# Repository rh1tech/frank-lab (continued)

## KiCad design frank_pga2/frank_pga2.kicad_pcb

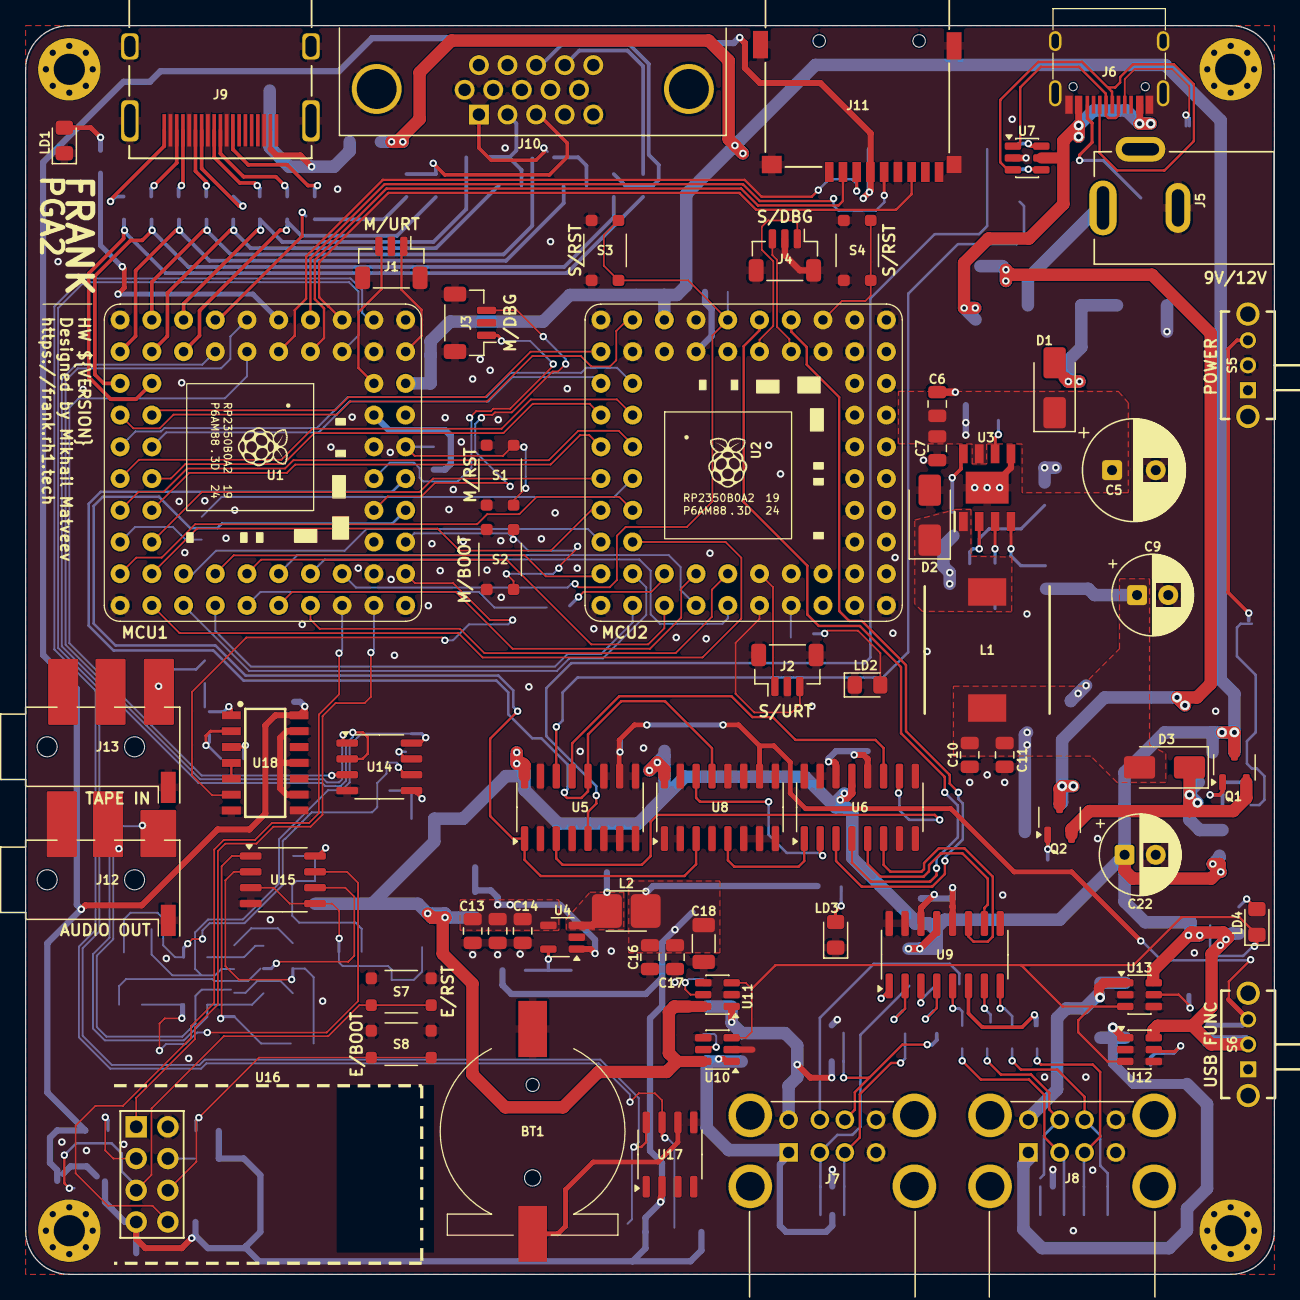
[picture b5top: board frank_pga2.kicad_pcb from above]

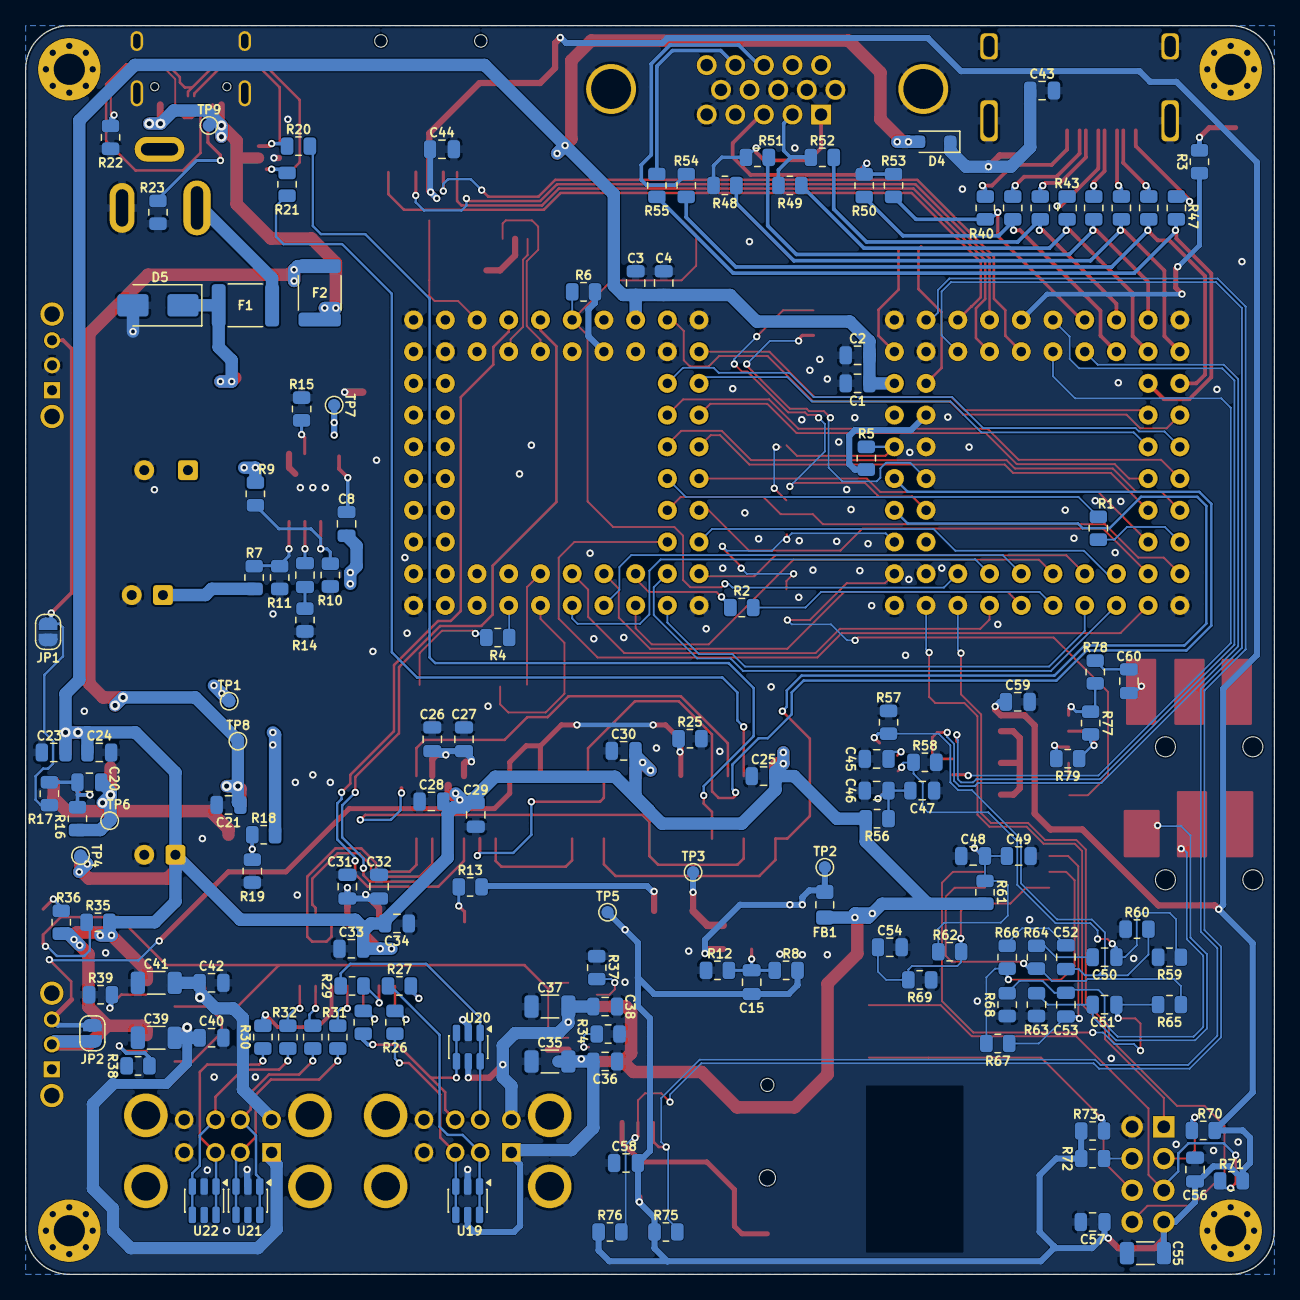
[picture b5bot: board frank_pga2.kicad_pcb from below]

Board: 2 copper layers, 100.0 x 100.0 mm, 212 parts (144 on the bottom side), 173 nets.

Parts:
BT1: Battery_CR1220
C1, C3, C10, C11, C12, C13, C16, C17, C21, C23, C45, C46, C48, C50, C51, C52, C53, C54, C56: 10u 16V; C_0805_2012Metric
C2, C4, C7, C8, C14, C24, C25, C27, C29, C30, C32, C34, C36, C38, C40, C42, C43, C44, C47, C49, C57, C58, C59, C60: 100n 50V; C_0805_2012Metric
C5: 680u 25V; C_Radial_D8.0mm_P3.50mm
C6: 10u 25V; C_0805_2012Metric
C9, C22: 220u 10V; C_Radial_D6.3mm_P2.50mm
C15: 22p 50V; C_0805_2012Metric
C18, C35, C37, C39, C41, C55: 100u 10V; C_1206_3216Metric
C19: 150p 50V; C_0805_2012Metric
C20, C26, C31: 1u 16V; C_0805_2012Metric
C28, C33: 4.7u 16V; C_0805_2012Metric
D1, D2, D3: SS34; D_SMA
D4: 1N5819WS; D_SOD-323
D5: SMAJ15A; D_SMA
F1, F2: 1.5A 24V; Fuse_1812_4532Metric
FB1: 600R@100MHz 2A; L_0805_2012Metric
H1, H2, H3, H4: Hole 2.5mm; MountingHole_2.5mm_Pad_Via
J1: UART M; JST_SH_1x03_P1.00mm_Vertical
J2: UART S; JST_SH_1x03_P1.00mm_Vertical
J3, J4: DEBUG; JST_SH_1x03_P1.00mm_Vertical
J5: DC 9-12V; BarrelJack_DC-005
J6: USB4215-03-A; USB_C_Receptacle
J7, J8: SS-52100-004; USB_A_Stacked
J9: DC3RX19JA2; HDMI_Female
J10: VGA; DSUB-15_Female
J11: 104031-0811; MicroSD_SMD_Long
J12: PJ-320D; AudioJack_3.5mm_PJ320D_AudioOut
J13: PJ-320D; AudioJack_3.5mm_PJ320D_TapeIn
JP1: Force On; SolderJumper-2_P1.3mm_Open_RoundedPad1.0x1.5mm
JP2: USB Debug; SolderJumper-2_P1.3mm_Open_RoundedPad1.0x1.5mm
L1: 22u; Inductor_CDRH104RNP
L2: 2.2u; L_Cenker_CKCS3015_HandSolder
LD1, LD2: Blue; LED_0805
LD3: Green; LED_0805
LD4: Red; LED_0805
Q1, Q2: AO3401A; SOT-23-3L_AOS
R1, R2: 33R; R_0805_2012Metric
R3, R4, R54, R55, R56, R61: 100R; R_0805_2012Metric
R5, R6, R17, R25, R59, R60, R62, R64, R66, R69, R70, R71, R72, R73: 10K; R_0805_2012Metric
R7, R65, R67: 47K; R_0805_2012Metric
R8, R9, R14, R15, R16, R19, R34, R35, R37, R38, R39, R77, R79: 100K; R_0805_2012Metric
R10: 30K; R_0805_2012Metric
R11: 8.2K; R_0805_2012Metric
R12: 22K; R_0805_2012Metric
R13, R18, R36, R51, R52, R53: 1K; R_0805_2012Metric
R20, R21, R26, R27, R28, R29, R30, R31, R32, R33: 22R; R_0805_2012Metric
R22, R23: 5.1K; R_0805_2012Metric
R40, R41, R42, R43, R44, R45, R46, R47: 270R; R_0805_2012Metric
R48, R49, R50: 330R; R_0805_2012Metric
R57, R58: 470R; R_0805_2012Metric
R63, R68: 20K; R_0805_2012Metric
R75, R76, R78: 4.7K; R_0805_2012Metric
S1, S3: RP Reset; Button_SMD_3x4x2mm
S2, S4: RP Boot; Button_SMD_3x4x2mm
S5: POWER; Switch_Slide_SK12D07VG3NS
S6: USB MODE; Switch_Slide_SK12D07VG3NS
S7: ESP Reset; Button_SMD_3x4x2mm
S8: ESP Boot; Button_SMD_3x4x2mm
TP1: +5V_DC; TestPoint_Pad_D1.0mm
TP2: +5V_BUCK; TestPoint_Pad_D1.0mm
TP3: LX; TestPoint_Pad_D1.0mm
TP4: VBUS; TestPoint_Pad_D1.0mm
TP5: +3V3; TestPoint_Pad_D1.0mm
TP6: +5V_SEL; TestPoint_Pad_D1.0mm
TP7: VIN_PROT; TestPoint_Pad_D1.0mm
TP8: VBUS_USB_F; TestPoint_Pad_D1.0mm
TP9: VBUS_USB; TestPoint_Pad_D1.0mm
U1, U2: Pimoroni PGA2350; PGA2350
U3: MP1584EN; SOIC-9_P1.27mm
U4: SY8089AAAC; SOT-23-5
U5, U8: 74HC4052D; SOP-16_P1.27mm
U6, U9: MW7211A; SOP-16_P1.27mm
U7, U19, U20, U21, U22: USBLC6-2SC6; SOT-23-6
U10, U11, U12, U13: CH217K; SOT-23-6
U14: TDA1387T; SO-8
U15: LM358; SO-8
U16: ESP-01 socket; ESP-01S
U17: DS3231MZ; SO-8
U18: CD4069UBM; SOIC-14_P1.27mm

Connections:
+3V3: C15.1, C16.1, C17.1, C18.1, C44.2, C55.1, C56.1, C57.1, C58.1, C59.1, J11.4 (VDD), L2.2, R8.1, R13.1, R70.1, R71.1, R72.1, R73.1, R75.2, R76.2, TP5.1 (1_1), U16.7 (VCC), U17.2 (VCC), U18.14 (VDD)
+5V_DC: C9.1, C10.1, C11.2, D3.2 (A), L1.2, R7.1, R18.1, TP1.1 (1_1)
+5V_SEL: C20.1, D3.1 (K), Q1.2 (S), Q2.2 (S), R16.1, TP6.1 (1_1)
/Audio/AMP_OUTL: C51.2, J12.T, R63.2
/Audio/AMP_OUTR: C53.2, J12.R, R68.2
/Audio/TDA_L: C50.1, R58.2, R59.1, U14.6 (A_LEFT)
/Audio/TDA_R: C52.1, R57.1, R60.1, U14.8 (A_RIGHT)
/ESP-01/ESP_EN: R70.2, U16.3 (CH_PD)
/ESP-01/ESP_GPIO0: R73.2, S8.1, S8.3, U16.6 (GPIO0)
/ESP-01/ESP_GPIO2: R72.2, U16.4 (GPIO2)
/ESP-01/ESP_RST: R71.2, S7.1, S7.3, U16.5 (RST)
/HUB2_UP_DM: U6.5 (DM2), U9.10 (DMU)
/HUB2_UP_DP: U6.6 (DP2), U9.11 (DPU)
/LED_M_A: LD1.2 (A), R3.2
/LED_S_A: LD2.2 (A), R4.2
/M0_UM_TX: J1.1, U1.61 (GP0)
/M1_UM_RX: J1.3, U1.62 (GP1)
/M2_RT_SDA: R76.1, U1.2 (GP2), U17.7 (SDA)
/M3_RT_SCL: R75.1, U1.3 (GP3), U17.8 (SCL)
/M4_SD_DAT0: J11.7 (DAT0), U1.4 (GP4)
/M5_SD_DAT3: J11.2 (DAT3/CD), U1.5 (GP5)
/M6_SD_CLK: J11.5 (CLK), U1.6 (GP6)
/M7_SD_CMD: J11.3 (CMD), U1.7 (GP7)
/M8_LD: R3.1, U1.8 (GP8)
/M9_AU_DATA: U1.9 (GP9), U14.3 (DATA)
/M10_AU_SCLK: U1.10 (GP10), U14.1 (SCLK)
/M11_AU_LRCK: U1.11 (GP11), U14.2 (LRCK)
/M12_HV_CLK-_B0: R40.2, R53.1, U1.12 (GP12)
/M13_HV_CLK+_B1: R41.2, R50.1, U1.13 (GP13)
/M14_HV_D0-_G0: R42.2, R52.1, U1.14 (GP14)
/M15_HV_D0+_G1: R43.2, R49.1, U1.15 (GP15)
/M16_HV_D1-_R0: R44.2, R51.1, U1.16 (GP16)
/M17_HV_D1+_R1: R45.2, R48.1, U1.17 (GP17)
/M18_HV_D2-_HS: R46.2, R54.2, U1.19 (GP18)
/M19_HV_D2+_VS: R47.2, R55.2, U1.20 (GP19)
/M20_S1_LK_A_D0: U1.21 (GP20), U2.62 (GP1)
/M21_S2_LK_A_D1: U1.22 (GP21), U2.2 (GP2)
/M22_S3_LK_A_D2: U1.23 (GP22), U2.3 (GP3)
/M23_S4_LK_A_D3: U1.24 (GP23), U2.4 (GP4)
/M24_S5_LK_A_D4: U1.25 (GP24), U2.5 (GP5)
/M25_S6_LK_A_D5: U1.26 (GP25), U2.6 (GP6)
/M26_S7_LK_A_D6: U1.27 (GP26), U2.7 (GP7)
/M27_S8_LK_A_D7: U1.28 (GP27), U2.8 (GP8)
/M28_LK_A_CLK: R1.2, U1.29 (GP28)
/M29_S10_LK_A_VALID: U1.30 (GP29), U2.10 (GP10)
/M30_S11_LK_B_D0: U1.31 (GP30), U2.11 (GP11)
/M31_S12_LK_B_D1: U1.32 (GP31), U2.12 (GP12)
/M32_S13_LK_B_D2: U1.34 (GP32), U2.13 (GP13)
/M33_S14_LK_B_D3: U1.35 (GP33), U2.14 (GP14)
/M34_S15_LK_B_D4: U1.36 (GP34), U2.15 (GP15)
/M35_S16_LK_B_D5: U1.37 (GP35), U2.16 (GP16)
/M36_S17_LK_B_D6: U1.38 (GP36), U2.17 (GP17)
/M37_S18_LK_B_D7: U1.39 (GP37), U2.19 (GP18)
/M38_LK_B_CLK: R2.2, U1.40 (GP38)
/M39_S20_LK_B_VALID: U1.41 (GP39), U2.21 (GP20)
/M40_S21_LK_FS: U1.42 (GP40), U2.22 (GP21)
/M41_S22_LK_DB_MS: U1.43 (GP41), U2.23 (GP22)
/M42_S23_LK_DB_SM: U1.44 (GP42), U2.24 (GP23)
/M43_S_LK_RUN: R6.2, S3.1, S3.3, U1.45 (GP43), U2.56 (RUN)
/M44_ES_RX: U1.46 (GP44), U16.8 (URXD)
/M45_ES_TX: U1.47 (GP45), U16.1 (UTXD)
/M46_TP_IN: U1.49 (GP46), U18.6 (I=*C)
/MCU Master/BOOTSEL: S2.1, S2.3, U1.51 (BOOTSEL)
/MCU Master/PGA_3V3: R5.1, U1.59 (3V3)
/MCU Master/RUN: R5.2, S1.1, S1.3, U1.56 (RUN)
/MCU Master/SWCLK: J3.3, U1.55 (SWCLK)
/MCU Master/SWDIO: J3.1, U1.52 (SWDIO)
/MCU Slave/BOOTSEL: S4.1, S4.3, U2.51 (BOOTSEL)
/MCU Slave/PGA_3V3: R6.1, U2.59 (3V3)
/MCU Slave/SWCLK: J4.3, U2.55 (SWCLK)
/MCU Slave/SWDIO: J4.1, U2.52 (SWDIO)
/M_USB_DM: U1.53 (USB_DM), U5.1 (2Y0), U8.3 (2Z)
/M_USB_DP: U1.54 (USB_DP), U5.12 (1Y0), U8.13 (1Z)
/Power/+5V_BUCK: C12.1, C13.1, C14.1, FB1.2, TP2.1 (1_1), U4.1 (EN), U4.4 (IN)
/Power/DC_FUSED: D1.2 (A), D5.1 (K), F1.2
/Power/FB: C15.2, R8.2, R12.1, U4.5 (FB)
/Power/VBUS_USB_F: C21.1, F2.2, Q2.3 (D), TP8.1 (1_1)
/Power/VIN_PROT: C5.1, C6.1, C7.1, D1.1 (K), R9.2, TP7.1 (1_1), U3.7 (VIN)
/S9_LK_A_CLK: R1.1, U2.9 (GP9)
/S19_LK_B_CLK: R2.1, U2.20 (GP19)
/S24_US_TX: J2.1, U2.25 (GP24)
/S25_US_RX: J2.3, U2.26 (GP25)
/S26_LD: R4.1, U2.27 (GP26)
/S_USB_DM: U2.53 (USB_DM), U6.3 (DM1)
/S_USB_DP: U2.54 (USB_DP), U6.4 (DP1)
/Tape In/TAPE: C60.2, J13.T
/USB-A/HUB2_VD33: C31.1, C32.1, U9.12 (VD33), U9.14 (VD3)
/USB-A/OC_LED_A: LD4.2 (A), R36.2
/USB-A/P0_DM: R27.1, U9.1 (DM0)
/USB-A/P0_DP: R26.1, U9.2 (DP0)
/USB-A/P1_DM: R29.1, U9.3 (DM1)
/USB-A/P1_DP: R28.1, U9.4 (DP1)
/USB-A/P2_DM: R31.1, U9.5 (DM2)
/USB-A/P2_DP: R30.1, U9.6 (DP2)
/USB-A/P3_DM: R33.1, U9.7 (DM3)
/USB-A/P3_DP: R32.1, U9.8 (DP3)
/USB-A/UA1_DM: J7.2 (D1-), R27.2, U19.1 (I/O1), U19.6 (I/O1)
/USB-A/UA1_DP: J7.3 (D1+), R26.2, U19.3 (I/O2), U19.4 (I/O2)
/USB-A/UA2_DM: J7.6 (D2-), R29.2, U20.1 (I/O1), U20.6 (I/O1)
/USB-A/UA2_DP: J7.7 (D2+), R28.2, U20.3 (I/O2), U20.4 (I/O2)
/USB-A/UA3_DM: J8.2 (D1-), R31.2, U21.3 (I/O2), U21.4 (I/O2)
/USB-A/UA3_DP: J8.3 (D1+), R30.2, U22.1 (I/O1), U22.6 (I/O1)
/USB-A/UA4_DM: J8.6 (D2-), R33.2, U21.1 (I/O1), U21.6 (I/O1)
/USB-A/UA4_DP: J8.7 (D2+), R32.2, U22.3 (I/O2), U22.4 (I/O2)
/USB-A/UA_ISET1: R34.1, U10.5 (ISET)
/USB-A/UA_ISET2: R37.1, U11.5 (ISET)
/USB-A/UA_ISET3: R38.1, U12.5 (ISET)
/USB-A/UA_ISET4: R39.1, U13.5 (ISET)
/USB-A/USB_OC: LD4.1 (K), R35.2, U10.3 (FLAG#), U11.3 (FLAG#), U12.3 (FLAG#), U13.3 (FLAG#)
/USB-A/VBUS_A1: C35.1, C36.1, J7.1 (VBUS1), U10.1 (VOUT), U19.5 (VBUS)
/USB-A/VBUS_A2: C37.1, C38.1, J7.5 (VBUS2), U11.1 (VOUT), U20.5 (VBUS)
/USB-A/VBUS_A3: C39.1, C40.1, J8.1 (VBUS1), U12.1 (VOUT)
/USB-A/VBUS_A4: C41.1, C42.1, J8.5 (VBUS2), U13.1 (VOUT)
/USB/HUB_P0_DM: U6.1 (DM0), U8.5 (2Y1)
/USB/HUB_P0_DP: U6.2 (DP0), U8.14 (1Y1)
/USB/HUB_UP_DM: U5.3 (2Z), U6.10 (DMU)
/USB/HUB_UP_DP: U5.13 (1Z), U6.11 (DPU)
/USB/HUB_VD33: C26.1, C27.1, U6.12 (VD33), U6.14 (VD3)
/USB/UC_CC1: J6.4 (CC1), R22.1
/USB/UC_CC2: J6.10 (CC2), R23.1
/USB/UC_DM: R20.1, U5.5 (2Y1)
/USB/UC_DM_C: J6.5 (DN2), J6.7 (DN1), U7.1 (I/O1)
/USB/UC_DM_E: R20.2, U7.6 (I/O1)
/USB/UC_DP: R21.1, U5.14 (1Y1)
/USB/UC_DP_C: J6.6 (DP1), J6.8 (DP2), U7.3 (I/O2)
/USB/UC_DP_E: R21.2, U7.4 (I/O2)
/USB/USB_MODE: JP2.2, R25.1, S6.3, U5.10 (S0), U8.10 (S0)
/VBUS_USB: F2.1, J6.2 (VBUS), J6.11 (VBUS), TP9.1 (1_1), U7.5 (VBUS)
GND: BT1.2 (-), C1.2, C2.2, C3.2, C4.2, C5.2, C6.2, C7.2, C9.2, C10.2, C11.1, C12.2, C13.2, C14.2, C16.2, C17.2, C18.2, C21.2, C22.2, C23.2, C24.2, C25.2, C26.2, C27.2, C28.2, C29.2, C30.2, C31.2, C32.2, C33.2, C34.2, C35.2, C36.2, C37.2, C38.2, C39.2, C40.2, C41.2, C42.2, C43.2, C44.1, C45.2, C46.2, C47.2, C48.2, C49.1, C54.1, C55.2, C56.2, C57.2, C58.2, C59.2, D2.2 (A), D5.2 (A), J1.2, J2.2, J3.2, J4.2, J5.2, J6.1 (GND), J6.12 (GND), J6.13 (SHIELD), J7.4 (GND1), J7.8 (GND2), J7.9 (Shield), J8.4 (GND1), J8.8 (GND2), J8.9 (Shield), J9.2 (G_D2), J9.5 (G_D1), J9.8 (G_D0), J9.11 (G_CLK), J9.17 (G_DDC/CEC), J9.20 (SHIELD1), J9.21 (SHIELD2), J9.22 (SHIELD3), J9.23 (SHIELD4), J10.0, J10.5, J10.6, J10.7, J10.8, J10.10, J11.6 (VSS), J11.SH (SHIELD), J12.S, J13.S, JP1.1, LD1.1 (K), LD2.1 (K), LD3.1 (K), R10.2, R11.1, R12.2, R14.2, R15.2, R19.2, R22.2, R23.2, R25.2, R34.2, R37.2, R38.2, R39.2, R57.2, R58.1, R59.2, R60.2, R63.1, R68.1, R69.1, S1.2, S1.4, S2.2, S2.4, S3.2, S3.4, S4.2, S4.4, S5.2, S7.2, S7.4, S8.2, S8.4, U1.1 (GND), U1.18 (GND), U1.33 (GND), U1.48 (GND), U2.1 (GND), U2.18 (GND), U2.33 (GND), U2.48 (GND), U3.5 (GND), U3.9 (EP), U4.2 (GND), U5.2 (2Y2), U5.4 (2Y3), U5.6 (~E), U5.7 (VEE), U5.8 (GND), U5.9 (S1), U5.11 (1Y3), U5.15 (1Y2), U6.15 (GND), U6.16 (GND), U7.2 (GND), U8.2 (2Y2), U8.4 (2Y3), U8.6 (~E), U8.7 (VEE), U8.8 (GND), U8.9 (S1), U8.11 (1Y3), U8.15 (1Y2), U9.15 (GND), U9.16 (GND), U10.2 (GND), U10.4 (EN#), U11.2 (GND), U11.4 (EN#), U12.2 (GND), U12.4 (EN#), U13.2 (GND), U13.4 (EN#), U14.4 (AGND), U15.4 (V-), U16.2 (GND), U17.5 (GND), U18.7 (VSS), U18.9 (D14), U18.11 (E), U18.13 (F), U19.2 (GND), U20.2 (GND), U21.2 (GND), U22.2 (GND)
unnamed: BT1.1 (+), U17.6 (VBAT)
unnamed: C19.2, R14.1
unnamed: C50.2, R64.2
unnamed: C51.1, R65.1, U15.7
unnamed: C52.2, R66.2
unnamed: C53.1, R67.1, U15.1
unnamed: C60.1, R78.2
unnamed: C8.2, D2.1 (K), L1.1, U3.1 (SW)
unnamed: C43.1, D4.1 (K), J9.18 (+5V)
unnamed: F1.1, J5.1
unnamed: J9.12 (CLKN), R40.1
unnamed: J9.10 (CLKP), R41.1
unnamed: J9.9 (D0N), R42.1
unnamed: J9.7 (D0P), R43.1
unnamed: J9.6 (D1N), R44.1
unnamed: J9.4 (D1P), R45.1
unnamed: J9.3 (D2N), R46.1
unnamed: J9.1 (D2P), R47.1
unnamed: J10.1, R48.2, R51.2
unnamed: J10.2, R49.2, R52.2
unnamed: J10.3, R50.2, R53.2
unnamed: J10.13, R54.1
unnamed: J10.14, R55.1
unnamed: JP1.2, R17.2, S5.3
unnamed: LD3.2 (A), R13.2
unnamed: C20.2, Q1.1 (G), R16.2, R17.1
unnamed: Q2.1 (G), R18.2, R19.1
unnamed: C8.1, U3.8 (BST)
unnamed: C19.1, U3.3 (COMP)
unnamed: R9.1, R10.1, U3.2 (EN)
unnamed: R7.2, R11.2, U3.4 (FB)
unnamed: R15.1, U3.6 (FREQ)
unnamed: L2.1, TP3.1 (1_1), U4.3 (LX)
unnamed: C45.1, U14.7 (FLT)
unnamed: C46.1, C47.1, R56.1, U14.5 (VA)
unnamed: C54.2, R62.1, R69.2, U15.3 (+), U15.5 (+)
unnamed: R66.1, R67.2, U15.2 (-)
unnamed: R64.1, R65.2, U15.6 (-)
unnamed: C48.1, C49.2, R61.2, R62.2, U15.8 (V+)
unnamed: R77.2, R78.1, U18.1 (A)
unnamed: R79.1, U18.3 (B)
unnamed: U18.4 (H=*B), U18.5 (C)
unnamed: R77.1, R79.2, U18.2 (G-*A)
VBUS: C1.1, C2.1, C3.1, C4.1, C22.1, C23.1, C24.1, C25.1, C28.1, C29.1, C30.1, C33.1, C34.1, D4.2 (A), FB1.1, JP2.1, Q1.3 (D), R35.1, R36.1, R56.2, R61.1, S6.2, TP4.1 (1_1), U1.60 (VBUS), U2.60 (VBUS), U5.16 (VCC), U6.13 (VDD5), U8.16 (VCC), U9.13 (VDD5), U10.6 (VIN), U11.6 (VIN), U12.6 (VIN), U13.6 (VIN)

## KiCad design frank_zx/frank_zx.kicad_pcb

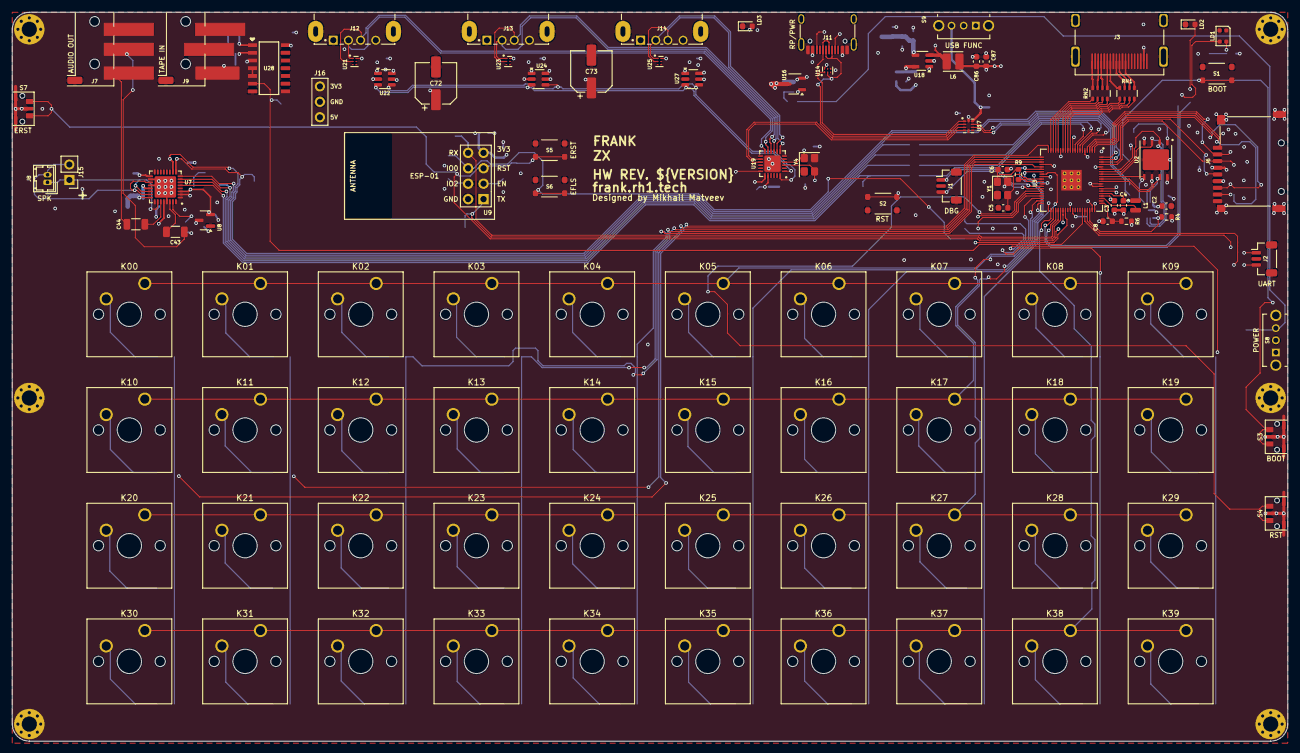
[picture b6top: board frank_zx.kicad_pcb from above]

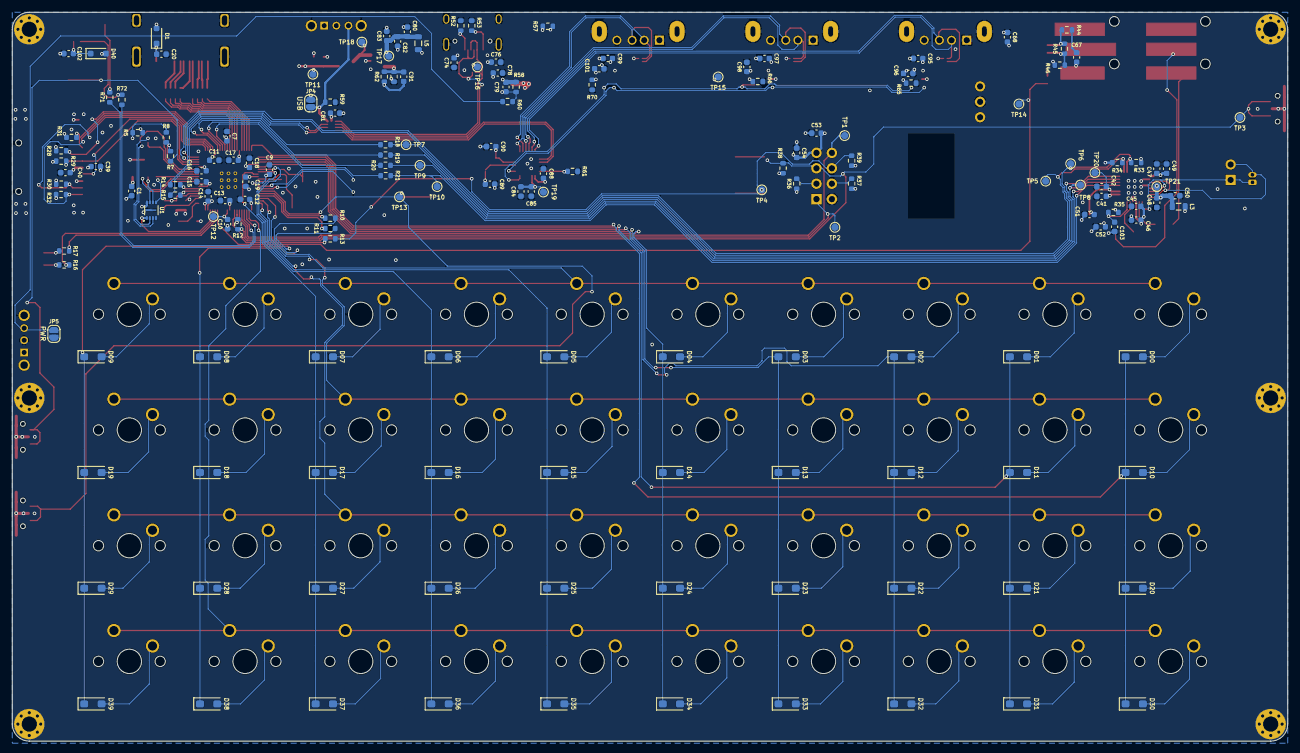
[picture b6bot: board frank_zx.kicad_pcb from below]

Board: 4 copper layers, 210.0 x 120.0 mm, 273 parts (164 on the bottom side), 179 nets.

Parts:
C1, C2, C7, C10, C11, C12, C13, C14, C15, C16, C17, C18, C19, C20, C40, C41, C42, C46, C49, C50, C54, C67, C68, C74, C79, C81, C83, C95, C97, C99, C102, C103: 100nF; C_0603_1608Metric
C3, C4, C8, C9: 4.7uF; C_0603_1608Metric
C5, C6: 15pF; C_0603_1608Metric
C39, C45, C47, C48, C53, C76, C78, C80, C82, C84, C86, C87, C88, C96, C98, C101: 10uF; C_0603_1608Metric
C43, C44: 100uF; C_1206_3216Metric
C51, C52, C85: 1uF; C_0603_1608Metric
C72, C73: 100uF; CP_Elec_6.3x6.0
C89, C90: 12pF; C_0603_1608Metric
C91: 22pF; C_0603_1608Metric
D00, D01, D02, D03, D04, D05, D06, D07, D08, D09, D10, D11, D12, D13, D14, D15, D16, D17, D18, D19, D20, D21, D22, D23, D24, D25, D26, D27, D28, D29, D30, D31, D32, D33, D34, D35, D36, D37, D38, D39: 1N4148W; D_SOD-123
D1, D40: 1N5819WS; D_SOD-323
H1, H2, H3, H4, H5, H6: MountingHole; MountingHole_2.5mm_Pad_Via
J1: Debug; JST_SH_1x03_P1.00mm_Vertical
J2: UART; JST_SH_1x03_P1.00mm_Vertical
J3: DC3RX19JA2; HDMI_Female
J6: 104031-0811; MicroSD_SMD_Long
J7: PJ-320D; AudioJack_3.5mm_PJ320D_AudioOut
J8: DF13-2P-1.25DSA; Hirose_DF13-02P-1.25DSA
J9: PJ-320D; AudioJack_3.5mm_PJ320D_TapeIn
J11: USB4215-03-A; USB_C_Receptacle
J12, J13, J14: 676430910; USB_A_Short
J15: Speaker; PinHeader_1x02_P2.54mm_Vertical
J16: PWR; PinHeader_1x03_P2.54mm
JP4: USB Debug; SolderJumper-2_P1.3mm_Open_RoundedPad1.0x1.5mm
JP5: PWR Debug; SolderJumper-2_P1.3mm_Open_RoundedPad1.0x1.5mm
K00, K01, K02, K03, K04, K05, K06, K07, K08, K09, K10, K11, K12, K13, K14, K15, K16, K17, K18, K19, K20, K21, K22, K23, K24, K25, K26, K27, K28, K29, K30, K31, K32, K33, K34, K35, K36, K37, K38, K39: MX; SW_Cherry_MX_1.00u_PCB
L1: 3.3µH; L_AOTA-B201610_2.0x1.6mm
L3, L5: 330R 2A; L_0805_2012Metric
L6: 2.2uH; L_Cenker_CKCS3015
LD1: WS2812B-2020; LED_WS2812B-2020_PLCC4_2.0x2.0mm
LD2: Blue; LED_0603_1608Metric
LD3: Green; LED_0603_1608Metric
R4, R5, R28, R29, R30, R31, R32, R35, R36, R37, R59, R60: 10K; R_0603_1608Metric
R6, R18, R19, R20, R21: 33R; R_0603_1608Metric
R7, R9, R57, R71: 1K; R_0603_1608Metric
R8: 0R; R_0603_1608Metric
R10, R11, R12, R13, R16, R17: 100R; R_0603_1608Metric
R14, R15: 27R; R_0603_1608Metric
R33, R34, R38, R39, R44, R61: 4.7K; R_0603_1608Metric
R45, R46, R58, R62, R65, R66, R70: 100K; R_0603_1608Metric
R52, R53: 5.1K; R_0603_1608Metric
R63: 22K; R_0603_1608Metric
R72: 330R; R_0603_1608Metric
RN1, RN2: 270R; R_Array_4x0603
S1: RP Boot; Button_SMD_3x4x2mm
S2: RP Reset; Button_SMD_3x4x2mm
S3: RP Boot; Button_SMD_TS1234VW
S4: RP Reset; Button_SMD_TS1234VW
S5: ESP Reset; Button_SMD_3x4x2mm
S6: ESP Flash; Button_SMD_3x4x2mm
S7: ESP Reset; Button_SMD_TS1234VW
S8, S9: SK12D07VG3NS; Switch_Slide_SK12D07VG3NS_PWR
TP1: GPIO36/TX; TestPoint_Pad_D1.2mm
TP2: GPIO37/RX; TestPoint_Pad_D1.2mm
TP3: GPIO38/ESP_RST; TestPoint_Pad_D1.2mm
TP4: GPIO39/ESP_BOOT; TestPoint_Pad_D1.2mm
TP5: GPIO2/SDA; TestPoint_Pad_D1.2mm
TP6: GPIO3/SCL; TestPoint_Pad_D1.2mm
TP7: GPIO8/MCLK; TestPoint_Pad_D1.2mm
TP8: GPIO9/BCLK; TestPoint_Pad_D1.2mm
TP9: GPIO10/WCLK; TestPoint_Pad_D1.2mm
TP10: GPIO11/DIN; TestPoint_Pad_D1.2mm
TP11: +3V3; TestPoint_Pad_D1.2mm
TP12: +1V1; TestPoint_Pad_D1.2mm
TP13: RUN; TestPoint_Pad_D1.2mm
TP14: GPIO44; TestPoint_Pad_D1.2mm
TP15: VBUS; TestPoint_Pad_D1.2mm
TP16: VBUS_IN; TestPoint_Pad_D1.2mm
TP17: +5V_BUCK; TestPoint_Pad_D1.2mm
TP18: LX; TestPoint_Pad_D1.2mm
TP19: VDD33; TestPoint_Pad_D1.2mm
TP20: +1V8; TestPoint_Pad_D1.2mm
TP21: +5V_SPK; TestPoint_Pad_D1.2mm
U1: APS6404L-3SQR-ZR; PSON50P200X300X50-9N
U2: W25Q128JVPIQ; WSON-8-1EP_6x5mm_P1.27mm_EP3.45x4.35mm
U3: RP2350B; RP2350-QFN-80_10x10_P0.4mm
U7: TLV320DAC3100IRHBR
U8: XC6206P182MR-G; SOT-23
U9: ESP-01v090; ESP-01S
U14, U21, U23, U25: TPD4S012DRYR
U16: AO3401A; SOT-23-3L_AOS
U17: TS3USB221RSER; UQFN-10
U18: SY8089AAAC; SOT-23-5
U19: CH334F; QFN-24-1EP_4x4mm_P0.5mm_EP2.7x2.7mm
U22, U24, U27: CH217K; SOT-23-6
U28: CD4069UBM; SOIC127P600X175-14N
Y1, Y4: 12 MHz; Crystal_SMD_3225-4Pin_3.2x2.5mm

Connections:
+1V1: C4.1, C7.1, C9.1, C10.1, L1.1, TP12.1, U3.10 (DVDD), U3.32 (DVDD), U3.51 (DVDD), U3.65 (VREG_FB)
+1V8: C42.2, C51.2, TP20.1, U7.3 (DVDD), U8.2 (VOUT)
+3V3: C1.1, C2.2, C3.1, C11.1, C12.1, C13.1, C14.1, C15.1, C16.1, C17.1, C18.1, C19.1, C39.2, C40.2, C41.1, C45.2, C46.2, C47.2, C49.2, C52.2, C53.1, C54.1, C68.1, C81.2, C86.1, C87.1, C91.1, J6.4 (VDD), J16.1, JP4.1 (A), L6.1, R4.2, R5.2, R6.1, R28.1, R29.1, R30.1, R31.2, R32.1, R33.2, R34.2, R35.2, R36.1, R37.1, R38.1, R39.1, R57.2, R62.1, S9.2, TP11.1, U1.8 (VDD), U2.8 (VCC), U3.5 (IOVDD), U3.15 (IOVDD), U3.24 (IOVDD), U3.29 (IOVDD), U3.41 (IOVDD), U3.50 (IOVDD), U3.59 (ADC_AVDD), U3.60 (IOVDD), U3.64 (VREG_VIN), U3.68 (USB_OTP_VDD), U3.69 (QSPI_IOVDD), U3.76 (IOVDD), U7.2 (IOVDD), U7.17 (AVDD), U7.28 (HPVDD), U8.3 (VIN), U9.7 (VCC), U17.10 (VCC), U28.14 (VDD)
/Audio/+5V_SPK: C48.2, C50.2, L3.1, TP21.1, U7.21 (SPKVDD_1), U7.24 (SPKVDD_2)
/Audio/CODEC_RST: C103.1, R35.1, U7.31 (~RESET)
/Audio/SPKM: J8.2, J15.2, U7.19 (SPKM_1), U7.23 (SPKM_2)
/Audio/SPKP: J8.1, J15.1, U7.22 (SPKP_1), U7.26 (SPKP_2)
/ESP01/CH_PD: R36.2, U9.3 (CH_PD)
/GPIO2/SDA: R34.1, TP5.1, U3.79 (GPIO2), U7.9 (SDA)
/GPIO3/SCL: R33.1, TP6.1, U3.80 (GPIO3), U7.10 (SCL)
/GPIO8/MCLK: R18.2, TP7.1, U7.8 (MCLK)
/GPIO9/BCLK: R19.2, TP8.1, U7.7 (BCLK)
/GPIO10/WCLK: R20.2, TP9.1, U7.6 (WCLK)
/GPIO11/DIN: R21.2, TP10.1, U7.5 (DIN)
/GPIO12/CLKN: RN1.4 (R4.1), U3.11 (GPIO12)
/GPIO13/CLKP: RN1.3 (R3.1), U3.12 (GPIO13)
/GPIO14/D0N: RN1.2 (R2.1), U3.13 (GPIO14)
/GPIO15/D0P: RN1.1 (R1.1), U3.14 (GPIO15)
/GPIO16/D1N: RN2.4 (R4.1), U3.16 (GPIO16)
/GPIO17/D1P: RN2.3 (R3.1), U3.17 (GPIO17)
/GPIO18/D2N: RN2.2 (R2.1), U3.18 (GPIO18)
/GPIO19/D2P: RN2.1 (R1.1), U3.19 (GPIO19)
/GPIO20/COL0: D00.1 (K), D10.1 (K), D20.1 (K), D30.1 (K), U3.20 (GPIO20)
/GPIO21/COL1: D01.1 (K), D11.1 (K), D21.1 (K), D31.1 (K), U3.21 (GPIO21)
/GPIO22/COL2: D02.1 (K), D12.1 (K), D22.1 (K), D32.1 (K), U3.22 (GPIO22)
/GPIO23/COL3: D03.1 (K), D13.1 (K), D23.1 (K), D33.1 (K), U3.23 (GPIO23)
/GPIO24/COL4: D04.1 (K), D14.1 (K), D24.1 (K), D34.1 (K), U3.25 (GPIO24)
/GPIO25/COL5: D05.1 (K), D15.1 (K), D25.1 (K), D35.1 (K), U3.26 (GPIO25)
/GPIO26/COL6: D06.1 (K), D16.1 (K), D26.1 (K), D36.1 (K), U3.27 (GPIO26)
/GPIO27/COL7: D07.1 (K), D17.1 (K), D27.1 (K), D37.1 (K), U3.28 (GPIO27)
/GPIO28/COL8: D08.1 (K), D18.1 (K), D28.1 (K), D38.1 (K), R10.2
/GPIO29/COL9: D09.1 (K), D19.1 (K), D29.1 (K), D39.1 (K), R11.2
/GPIO30/ROW0: K00.1, K01.1, K02.1, K03.1, K04.1, K05.1, K06.1, K07.1, K08.1, K09.1, U3.38 (GPIO30)
/GPIO31/ROW1: K10.1, K11.1, K12.1, K13.1, K14.1, K15.1, K16.1, K17.1, K18.1, K19.1, U3.39 (GPIO31)
/GPIO32/ROW2: K20.1, K21.1, K22.1, K23.1, K24.1, K25.1, K26.1, K27.1, K28.1, K29.1, U3.40 (GPIO32)
/GPIO33/ROW3: K30.1, K31.1, K32.1, K33.1, K34.1, K35.1, K36.1, K37.1, K38.1, K39.1, U3.42 (GPIO33)
/GPIO36/TX: TP1.1, U3.45 (GPIO36), U9.8 (URXD)
/GPIO37/RX: TP2.1, U3.46 (GPIO37), U9.1 (UTXD)
/GPIO38/ESP_RST: R12.2, R38.2, S5.1, S5.3, S7.1, TP3.1, U9.5 (RST)
/GPIO39/ESP_BOOT: R13.2, R39.2, S6.1, S6.3, TP4.1, U9.6 (GPIO0)
/RP2350B/BOOT: R7.2, S1.1, S1.3, S3.1
/RP2350B/D+: R14.1, U17.8 (D+)
/RP2350B/D-: R15.1, U17.7 (D-)
/RP2350B/GPIO44: TP14.1, U3.55 (GPIO44_ADC4), U28.6 (I=*C)
/RP2350B/GPIO45: R17.2, U3.56 (GPIO45_ADC5)
/RP2350B/GPIO46: R16.2, U3.57 (GPIO46_ADC6)
/RP2350B/GPIO47: R4.1, U1.1 (~CE), U3.58 (GPIO47_ADC7)
/RP2350B/LED: R71.1, U3.43 (GPIO34)
/RP2350B/QSPI_SCLK: U1.6 (SCLK), U2.6 (CLK), U3.71 (QSPI_SCLK)
/RP2350B/QSPI_SD0: U1.5 (SI/SIO(0)), U2.5 (DI_(IO0)), U3.72 (QSPI_SD0)
/RP2350B/QSPI_SD1: U1.2 (SO/SIO(1)), U2.2 (DO_(IO1)), U3.74 (QSPI_SD1)
/RP2350B/QSPI_SD2: U1.3 (SIO(2)), U2.3 (~WP_(IO2)), U3.73 (QSPI_SD2)
/RP2350B/QSPI_SD3: U1.7 (SIO(3)), U2.7 (~HOLD_OR_/RESET_(IO3)), U3.70 (QSPI_SD3)
/RP2350B/QSPI_SS: R7.1, R8.1, U3.75 (QSPI_SS)
/RP2350B/RGB_LED: R72.1, U3.44 (GPIO35)
/RP2350B/RUN: S2.1, S2.3, S4.1, TP13.1, U3.35 (RUN)
/RP2350B/SWCLK: J1.1 (Pin_3_3), U3.33 (SWCLK)
/RP2350B/SWD: J1.3 (Pin_1_1), U3.34 (SWD)
/RP2350B/VREG_AVDD: C8.1, R6.2, U3.61 (VREG_AVDD)
/RP2350B/VREG_LX: L1.2, U3.63 (VREG_LX)
/RP2350B/XIN: C5.1, U3.30 (XIN), Y1.3
/RP2350B/XOUT: R9.2, U3.31 (XOUT)
/SD/CD_DAT3/GPIO7: J6.2 (DAT3/CD), R28.2, U3.4 (GPIO7)
/SD/CLK/GPIO1: J6.5 (CLK), U3.78 (GPIO1)
/SD/CMD/GPIO0: J6.3 (CMD), R29.2, U3.77 (GPIO0)
/SD/DAT0/GPIO4: J6.7 (DAT0), R30.2, U3.1 (GPIO4)
/SD/DAT1/GPIO5: J6.8 (DAT1), R32.2, U3.2 (GPIO5)
/SD/DAT2/GPIO6: J6.1 (DAT2), R31.1, U3.3 (GPIO6)
/Tape/TAPE: C67.2, J9.T
/USB/+5V_BUCK: C80.1, C82.1, C83.1, L5.2, TP17.1, U18.1 (EN), U18.4 (IN)
/USB/DH+: U17.3 (2D+), U19.15 (DPU+)
/USB/DH-: U17.4 (2D-), U19.14 (DMU-)
/USB/DS1+: J12.3 (D+), U19.12 (DP1+), U21.1 (D+)
/USB/DS1-: J12.2 (D-), U19.11 (DM1-), U21.2 (D-_)
/USB/DS2+: J13.3 (D+), U19.10 (DP2+), U23.1 (D+)
/USB/DS2-: J13.2 (D-), U19.9 (DM2-), U23.2 (D-_)
/USB/DS3+: J14.3 (D+), U19.8 (DP3+), U25.1 (D+)
/USB/DS3-: J14.2 (D-), U19.7 (DM3-), U25.2 (D-_)
/USB/LX: L6.2, TP18.1, U18.3 (LX)
/USB/OVCUR: U19.1 (~OVCUR), U22.3 (FLAG#), U24.3 (FLAG#), U27.3 (FLAG#)
/USB/PWREN: U19.24 (~PWREN), U22.4 (EN#), U24.4 (EN#), U27.4 (EN#)
/USB/S: JP4.2 (B), R59.2, S9.3, U17.9 (S)
/USB/USB A Port 1/VBUS_P: C95.1, J12.1 (VBUS), U21.6 (VBUS), U22.1 (VOUT)
/USB/USB A Port 2/VBUS_P: C97.1, J13.1 (VBUS), U23.6 (VBUS), U24.1 (VOUT)
/USB/USB A Port 3/VBUS_P: C99.1, J14.1 (VBUS), U25.6 (VBUS), U27.1 (VOUT)
/USB/USBC_D+: J11.6 (DP1), J11.8 (DP2), U14.1 (D+), U17.1 (1D+)
/USB/USBC_D-: J11.5 (DN2), J11.7 (DN1), U14.2 (D-_), U17.2 (1D-)
/USB/VBUS_IN: C74.2, C76.2, C78.1, C79.2, J11.2 (VBUS), J11.11 (VBUS), R58.2, TP16.1, U14.6 (VBUS), U16.2 (S)
/USB/VDD33: C84.2, C85.2, TP19.1, U19.20 (VDD33_{LDO})
/USB/XTAL_N: C89.1, U19.3 (XO), Y4.3
/USB/XTAL_P: C90.1, U19.4 (XI), Y4.1
GND: C1.2, C2.1, C3.2, C4.2, C5.2, C6.2, C7.2, C8.2, C9.2, C10.2, C11.2, C12.2, C13.2, C14.2, C15.2, C16.2, C17.2, C18.2, C19.2, C20.2, C39.1, C40.1, C41.2, C42.1, C45.1, C46.1, C47.1, C48.1, C49.1, C50.1, C51.1, C52.1, C53.2, C54.2, C68.2, C72.2, C73.2, C74.1, C76.1, C78.2, C80.2, C81.1, C82.2, C83.2, C84.1, C85.1, C86.2, C87.2, C88.1, C89.2, C90.2, C95.2, C96.1, C97.2, C98.1, C99.2, C101.1, C102.2, C103.2, H1.1 (1_1), H2.1 (1_1), H3.1 (1_1), H4.1 (1_1), H5.1 (1_1), H6.1 (1_1), J1.2 (Pin_2_2), J2.2 (Pin_2_2), J3.2 (G_D2), J3.5 (G_D1), J3.8 (G_D0), J3.11 (G_CLK), J3.17 (G_DDC/CEC), J3.20 (SHIELD1), J3.21 (SHIELD2), J3.22 (SHIELD3), J3.23 (SHIELD4), J6.6 (VSS), J6.SH (SHIELD), J7.S, J9.S, J11.1 (GND), J11.12 (GND), J11.13 (SHIELD), J12.4 (GND), J12.5 (Shield), J13.4 (GND), J13.5 (Shield), J14.4 (GND), J14.5 (Shield), J16.2, JP5.1 (A), LD1.2 (VSS), LD2.1 (K), LD3.1 (K), R52.1, R53.1, R59.1, R61.2, R63.2, R65.1, R66.1, R70.1, S1.2, S1.4, S2.2, S2.4, S3.2, S3.3 (GND), S4.2, S4.3 (GND), S5.2, S5.4, S6.2, S6.4, S7.2, S7.3 (GND), S8.2, U1.4 (VSS), U1.9 (EXP), U2.4 (GND_1), U2.9 (GND_2), U3.62 (VREG_PGND), U3.81 (GND), U7.1 (IOVSS), U7.16 (AVSS), U7.18 (DVSS), U7.20 (SPKVSS_1), U7.25 (SPKVSS_2), U7.29 (HPVSS), U7.33 (EP), U8.1 (VSS), U9.2 (GND), U14.4 (GND), U17.5 (GND), U17.6 (~OE), U18.2 (GND), U19.25 (GND), U21.4 (GND), U22.2 (GND), U23.4 (GND), U24.2 (GND), U25.4 (GND), U27.2 (GND), U28.7 (VSS), U28.9 (D), U28.11 (E), U28.13 (F), Y1.2, Y1.4, Y4.2, Y4.4
unnamed: C6.1, R9.1, Y1.1
unnamed: C43.1, J7.R
unnamed: C44.1, J7.T
unnamed: C67.1, R44.2
unnamed: D00.2 (A), K00.2
unnamed: D01.2 (A), K01.2
unnamed: C20.1, D1.1 (K), J3.18 (+5V)
unnamed: D02.2 (A), K02.2
unnamed: D03.2 (A), K03.2
unnamed: D04.2 (A), K04.2
unnamed: D05.2 (A), K05.2
unnamed: D06.2 (A), K06.2
unnamed: D07.2 (A), K07.2
unnamed: D08.2 (A), K08.2
unnamed: D09.2 (A), K09.2
unnamed: D10.2 (A), K10.2
unnamed: D11.2 (A), K11.2
unnamed: D12.2 (A), K12.2
unnamed: D13.2 (A), K13.2
unnamed: D14.2 (A), K14.2
unnamed: D15.2 (A), K15.2
unnamed: D16.2 (A), K16.2
unnamed: D17.2 (A), K17.2
unnamed: D18.2 (A), K18.2
unnamed: D19.2 (A), K19.2
unnamed: D20.2 (A), K20.2
unnamed: D21.2 (A), K21.2
unnamed: D22.2 (A), K22.2
unnamed: D23.2 (A), K23.2
unnamed: D24.2 (A), K24.2
unnamed: D25.2 (A), K25.2
unnamed: D26.2 (A), K26.2
unnamed: D27.2 (A), K27.2
unnamed: D28.2 (A), K28.2
unnamed: D29.2 (A), K29.2
unnamed: D30.2 (A), K30.2
unnamed: D31.2 (A), K31.2
unnamed: D32.2 (A), K32.2
unnamed: D33.2 (A), K33.2
unnamed: D34.2 (A), K34.2
unnamed: D35.2 (A), K35.2
unnamed: D36.2 (A), K36.2
unnamed: D37.2 (A), K37.2
unnamed: D38.2 (A), K38.2
unnamed: D39.2 (A), K39.2
unnamed: C102.1, D40.1 (K), LD1.4 (VDD)
unnamed: J2.1 (Pin_3_3), R17.1
unnamed: J2.3 (Pin_1_1), R16.1
unnamed: J3.12 (CLKN), RN1.5 (R4.2)
unnamed: J3.10 (CLKP), RN1.6 (R3.2)
unnamed: J3.9 (D0N), RN1.7 (R2.2)
unnamed: J3.7 (D0P), RN1.8 (R1.2)
unnamed: J3.6 (D1N), RN2.5 (R4.2)
unnamed: J3.4 (D1P), RN2.6 (R3.2)
unnamed: J3.3 (D2N), RN2.7 (R2.2)
unnamed: J3.1 (D2P), RN2.8 (R1.2)
unnamed: J11.4 (CC1), R52.2
unnamed: J11.10 (CC2), R53.2
unnamed: JP5.2 (B), R60.2, S8.3
unnamed: LD1.3 (DIN), R72.2
unnamed: LD2.2 (A), R71.2
unnamed: LD3.2 (A), R57.1
unnamed: R5.1, R8.2, U2.1 (~CS)
unnamed: R18.1, U3.6 (GPIO8)
unnamed: R19.1, U3.7 (GPIO9)
unnamed: R20.1, U3.8 (GPIO10)
unnamed: R21.1, U3.9 (GPIO11)
unnamed: R10.1, U3.36 (GPIO28)
unnamed: R11.1, U3.37 (GPIO29)
unnamed: R12.1, U3.47 (GPIO38)
unnamed: R13.1, U3.48 (GPIO39)
unnamed: R15.2, U3.66 (USB_DM)
unnamed: R14.2, U3.67 (USB_DP)
unnamed: C44.2, U7.27 (HPL)
unnamed: C43.2, U7.30 (HPR)
unnamed: R37.2, U9.4 (GPIO2)
unnamed: C79.1, R58.1, R60.1, U16.1 (G)
unnamed: C91.2, R62.2, R63.1, U18.5 (FB)
unnamed: R61.1, U19.18 (PSELF)
unnamed: R65.2, U22.5 (ISET)
unnamed: R66.2, U24.5 (ISET)
unnamed: R70.2, U27.5 (ISET)
unnamed: R44.1, R45.2, U28.1 (A)
unnamed: R46.1, U28.3 (B)
unnamed: U28.4 (H=*B), U28.5 (C)
unnamed: R45.1, R46.2, U28.2 (G-*A)
VBUS: C72.1, C73.1, C88.2, C96.2, C98.2, C101.2, D1.2 (A), D40.2 (A), J16.3, L3.2, L5.1, TP15.1, U16.3 (D), U19.19 (V5), U22.6 (VIN), U24.6 (VIN), U27.6 (VIN)

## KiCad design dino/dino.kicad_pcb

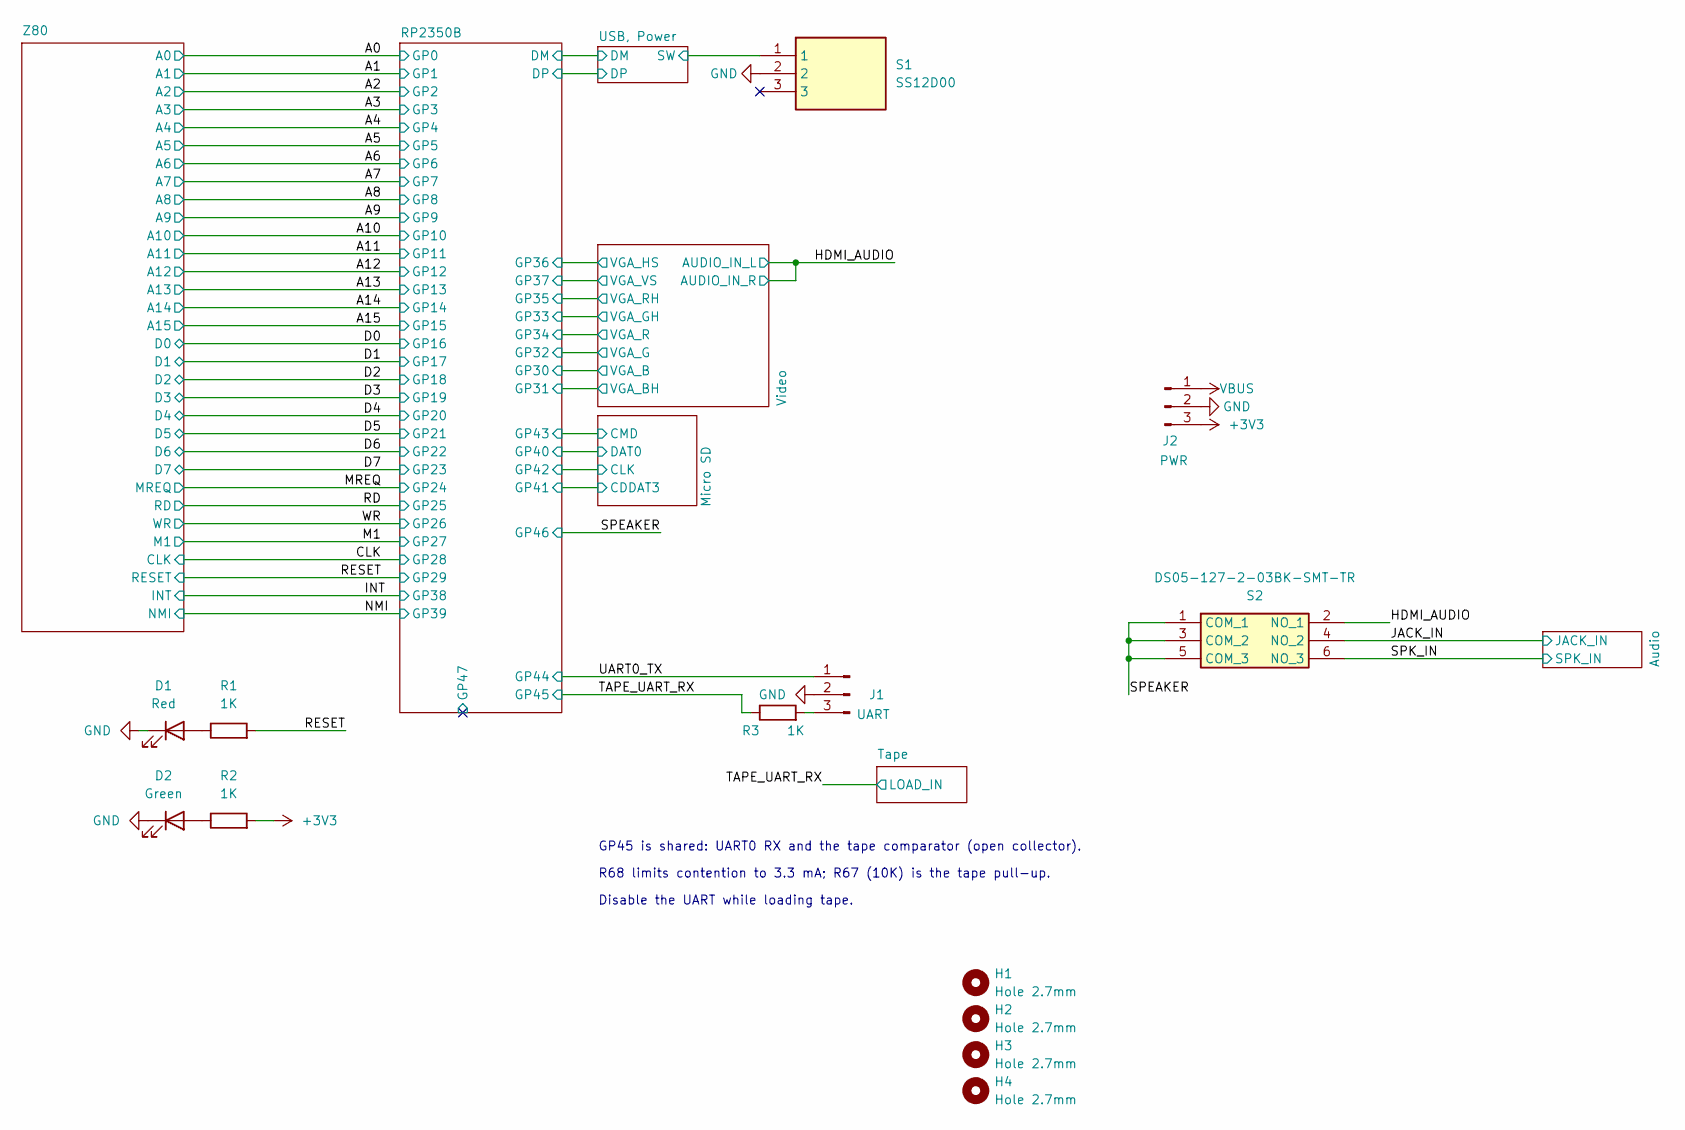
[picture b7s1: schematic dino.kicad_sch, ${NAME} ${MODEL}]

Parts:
D1: Red; LED_0805_2012Metric_Pad1.15x1.40mm_HandSolder
D2: Green; LED_0805_2012Metric_Pad1.15x1.40mm_HandSolder
H1, H2, H3, H4: Hole 2.7mm; MountingHole_2.7mm
J1: UART; JST_SH_1x03_P1.00mm_Vertical
J2: PWR; PinHeader_1x03_P2.54mm_Vertical
R1, R2, R3: 1K; R_0603_1608Metric
S1: SS12D00; Switch_Slide_SS12D00; Mouser Part Number 611-SK12D07VG3NS
S2: DS05-127-2-03BK-SMT-TR; SW_DIP_DS05-127-2-03BK-SMT

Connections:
+3V3: J2.3, R2.2; also elsewhere on the board
/HDMI_AUDIO: S2.2 (NO_1); also elsewhere on the board
/JACK_IN: S2.4 (NO_2); also elsewhere on the board
/RESET: R1.2; also elsewhere on the board
/SPEAKER: S2.1 (COM_1), S2.3 (COM_2), S2.5 (COM_3); also elsewhere on the board
/SPK_IN: S2.6 (NO_3); also elsewhere on the board
/TAPE_UART_RX: R3.1; also elsewhere on the board
/UART0_TX: J1.1; also elsewhere on the board
/USB, Power/SW: S1.1; also elsewhere on the board
GND: D1.1 (K), D2.1 (K), J1.2, J2.2, S1.2; also elsewhere on the board
unnamed: D1.2 (A), R1.1
unnamed: D2.2 (A), R2.1
unnamed: J1.3, R3.2
VBUS: J2.1; also elsewhere on the board

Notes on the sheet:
Disable the UART while loading tape.
R68 limits contention to 3.3 mA; R67 (10K) is the tape pull-up.
GP45 is shared: UART0 RX and the tape comparator (open collector).
